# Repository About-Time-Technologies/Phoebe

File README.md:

# Phoebe
Core microcontroller board for all main projects

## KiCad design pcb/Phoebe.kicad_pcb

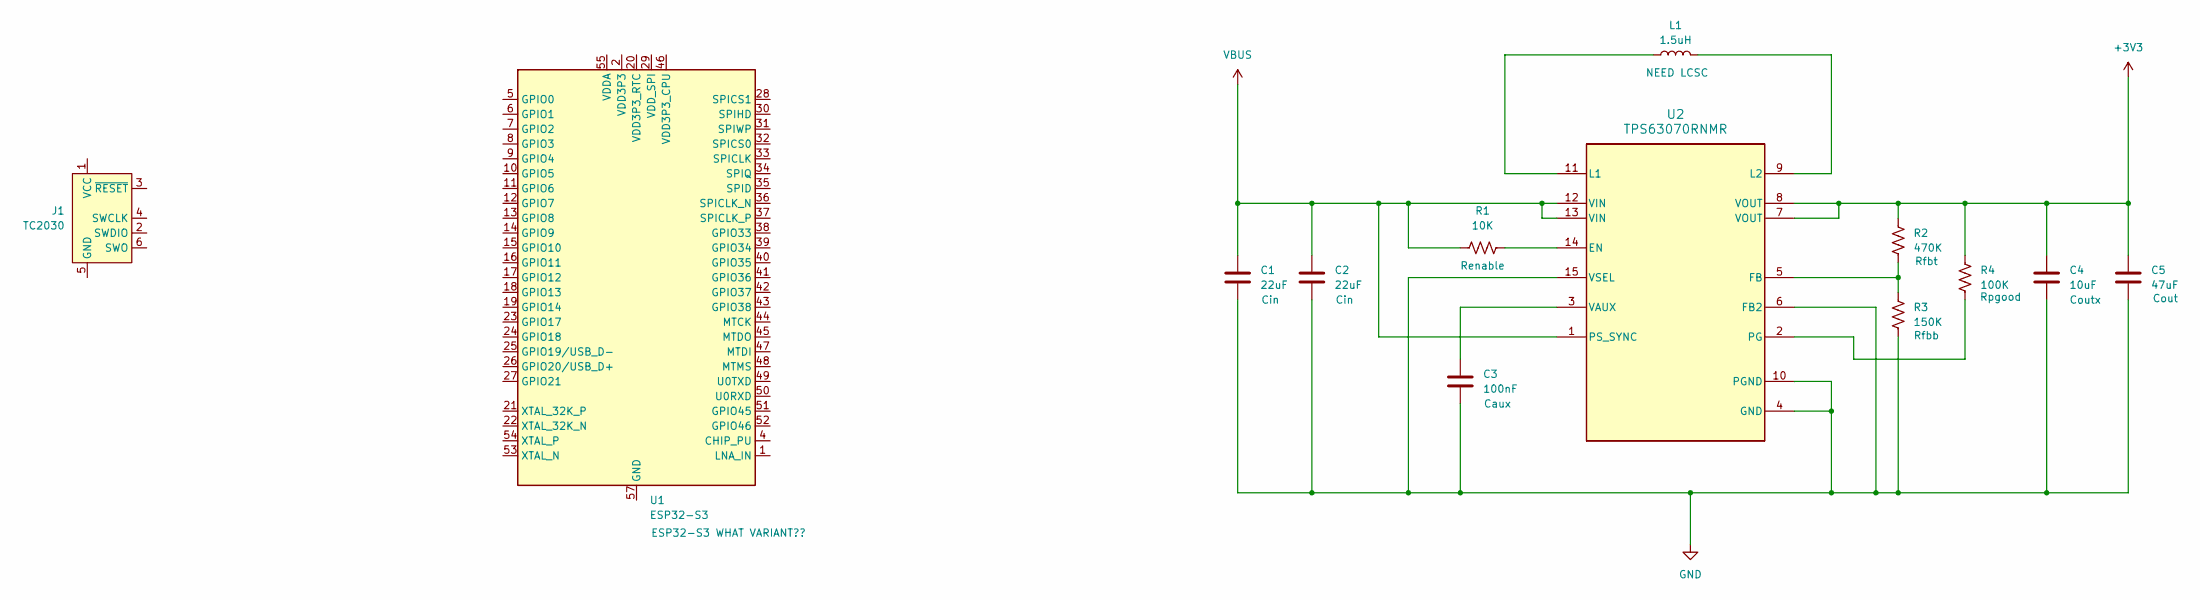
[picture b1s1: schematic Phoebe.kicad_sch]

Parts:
C1, C2: 22uF; C_1206_3216Metric; LCSC C12891
C3: 100nF; C_0402_1005Metric; LCSC C1525
C4: 10uF; C_0603_1608Metric; LCSC C96446
C5: 47uF; C_1206_3216Metric; LCSC C16780
J1: TC2030; Tag-Connect_TC2030-IDC-NL_2x03_P1.27mm_Vertical
L1: 1.5uH; L_Coilcraft_XAL4020-XXX
R1: 10K; R_0402_1005Metric; LCSC C25744
R2: 470K; R_0603_1608Metric; LCSC C23178
R3: 150K; R_0603_1608Metric; LCSC C22807
R4: 100K; R_0603_1608Metric; LCSC C25803
U1: ESP32-S3; QFN-56-1EP_7x7mm_P0.4mm_EP4x4mm
U2: TPS63070RNMR; RNM0015A; LCSC C109322

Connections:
+3V3: C4.1, C5.1, R2.1, R4.1, U2.7 (VOUT), U2.8 (VOUT)
GND: C1.2, C2.2, C3.2, C4.2, C5.2, R3.2, U2.4 (GND), U2.6 (FB2), U2.10 (PGND), U2.15 (VSEL)
unnamed: U1.2 (VDD3P3), U1.3 (VDD3P3)
unnamed: U1.55 (VDDA), U1.56 (VDDA)
unnamed: R1.2, U2.14 (EN)
unnamed: R2.2, R3.1, U2.5 (FB)
unnamed: L1.1, U2.11 (L1)
unnamed: L1.2, U2.9 (L2)
unnamed: R4.2, U2.2 (PG)
unnamed: C3.1, U2.3 (VAUX)
VBUS: C1.1, C2.1, R1.1, U2.1 (PS_SYNC), U2.12 (VIN), U2.13 (VIN)

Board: 2 copper layers, 13 parts (0 on the bottom side), 11 nets, no tracks yet.

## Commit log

2024-05-25 Power Regulator
